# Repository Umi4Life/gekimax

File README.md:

# gekimax

generic rhythm game keypad controller with a lever

## BOM (LCSC, also see [the csv](gekimax-pcb/gekimax.csv))

| Part | Amount |
|---|---|
| RK09L11 Rotary Potentiometer | 1 |
| 100nF Capacitor 0805 | 28 |
| SK6812MINI-E LED | 21 |
| USB-C Connector | 5 |
| 220Ω Resistor 0603 | 1 |
| 5.1KΩ Resistor 0603 | 2 |

*RK09 potentiometer may need some disassembly and modding to remove detent*

## BOM (Additional Hardware)

| Part | Amount |
|---|---|
| Raspberry Pi Pico | 1 |
| M3 Heat Insert | 6 |
| M3 Nut | 2 |
| M3x15-16mm Countersunk Screw | 8 |
| M3x40 Button Head Screw | 1 |
| Rubber Feet | 4 |
| Rubber sheet/padding for lever | 1 |
| Keyboard Switches | 21 |
| Hot Swap Socket | 21 |
| Plate Mount Stabilizer | 4 |
| 1U keycaps | 8 |
| 1.25U keycaps | 9 |
| 2U keycaps | 2 |
| 2.75U keycaps | 2 |

## Notes
- Uses [GP2040-CE](https://gp2040-ce.info/) for firmware (need some manual key mapping)
- PCB has some additional side leds that I couldn't get them to work

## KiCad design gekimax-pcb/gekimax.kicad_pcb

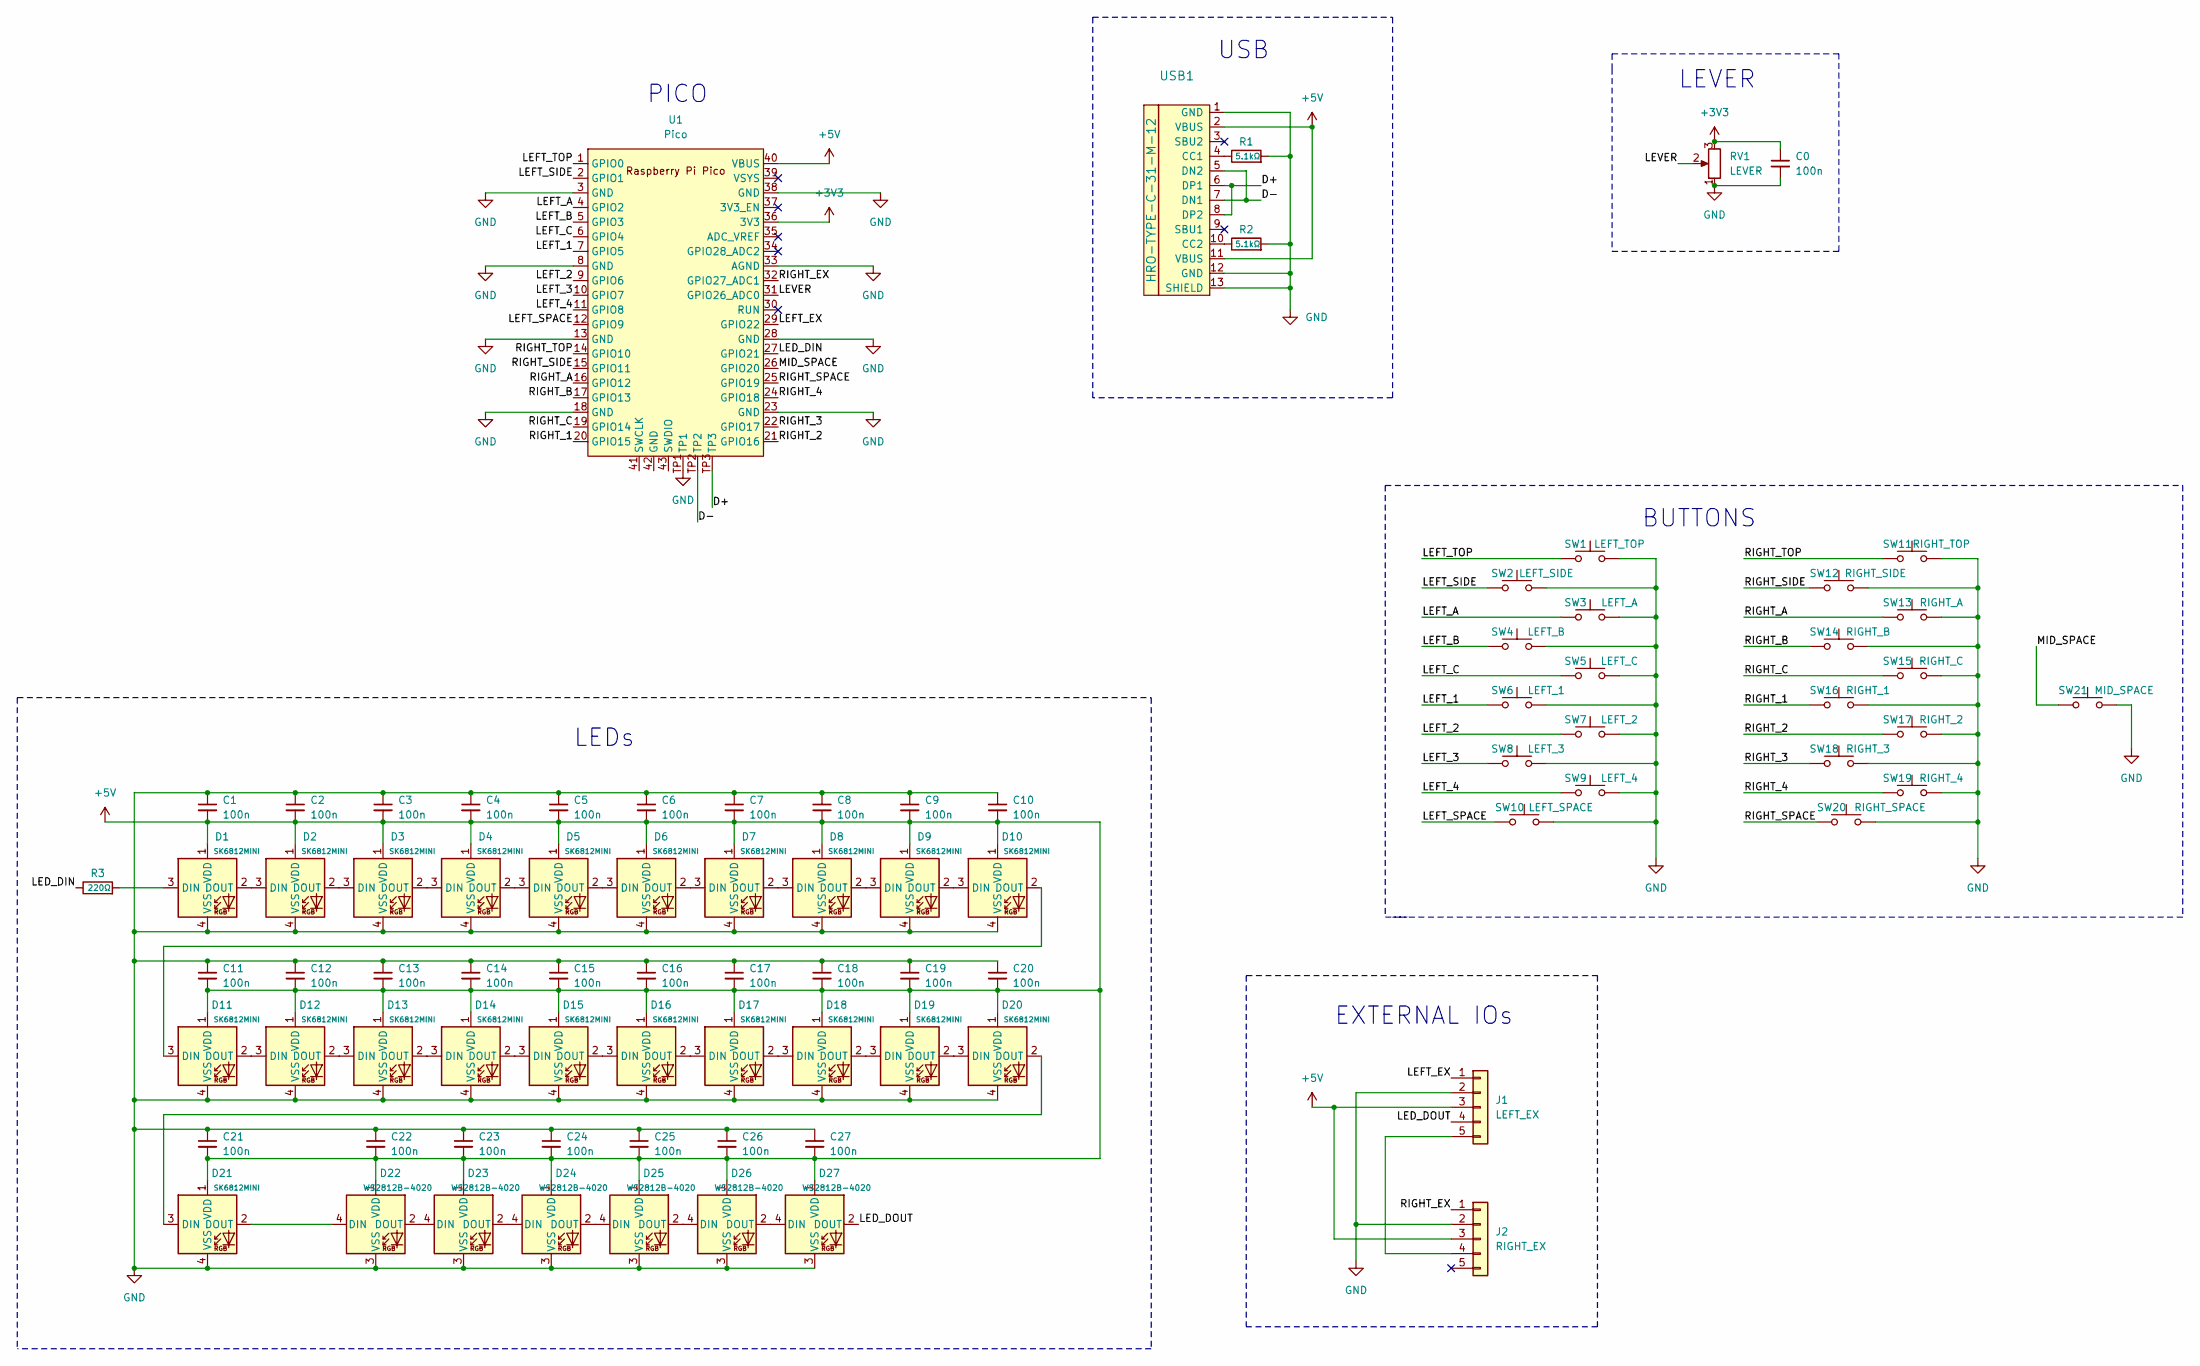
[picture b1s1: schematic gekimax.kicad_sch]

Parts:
C0, C1, C2, C3, C4, C5, C6, C7, C8, C9, C10, C11, C12, C13, C14, C15, C16, C17, C18, C19, C20, C21, C22, C23, C24, C25, C26, C27: 100n; C_0805_2012Metric_Pad1.18x1.45mm_HandSolder; LCSC C48579599
D1, D2, D3, D4, D5, D6, D7, D8, D9, D10, D11, D12, D13, D14, D15, D16, D17, D18, D19, D20, D21: SK6812MINI; LED_MX_6028R; LCSC C5149201
D22, D23, D24, D25, D26, D27: WS2812B-4020; LED_WS2812_4020; LCSC C965557
J1: LEFT_EX; JST_GH_SM05B-GHS-TB_1x05-1MP_P1.25mm_Horizontal; LCSC C189896
J2: RIGHT_EX; JST_GH_SM05B-GHS-TB_1x05-1MP_P1.25mm_Horizontal; LCSC C189896
R1, R2: 5.1kΩ; R_0603_1608Metric_Pad0.98x0.95mm_HandSolder; LCSC C2907044
R3: 220Ω; R_0603_1608Metric_Pad0.98x0.95mm_HandSolder; LCSC C107696
RV1: LEVER; Potentiometer_Alps_RK09L_Single_Horizontal; LCSC C2830189
SW1: LEFT_TOP; MX-Hotswap-1.25U
SW2: LEFT_SIDE; MX-Hotswap-2U
SW3: LEFT_A; MX-Hotswap-1.25U
SW4: LEFT_B; MX-Hotswap-1.25U
SW5: LEFT_C; MX-Hotswap-1.25U
SW6: LEFT_1; MX-Hotswap-1U
SW7: LEFT_2; MX-Hotswap-1U
SW8: LEFT_3; MX-Hotswap-1U
SW9: LEFT_4; MX-Hotswap-1U
SW10: LEFT_SPACE; MX-Hotswap-2U
SW11: RIGHT_TOP; MX-Hotswap-1.25U
SW12: RIGHT_SIDE; MX-Hotswap-2U
SW13: RIGHT_A; MX-Hotswap-1.25U
SW14: RIGHT_B; MX-Hotswap-1.25U
SW15: RIGHT_C; MX-Hotswap-1.25U
SW16: RIGHT_1; MX-Hotswap-1U
SW17: RIGHT_2; MX-Hotswap-1U
SW18: RIGHT_3; MX-Hotswap-1U
SW19: RIGHT_4; MX-Hotswap-1U
SW20: RIGHT_SPACE; MX-Hotswap-2U
SW21: MID_SPACE; MX-Hotswap-2U
U1: Pico; RPi_Pico_SMD
USB1: HRO-TYPE-C-31-M-12; HRO-TYPE-C-31-M-12-HandSoldering; LCSC C167321

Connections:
+3V3: C0.1, RV1.3, U1.36 (3V3)
+5V: C1.2, C2.2, C3.2, C4.2, C5.2, C6.2, C7.2, C8.2, C9.2, C10.2, C11.2, C12.2, C13.2, C14.2, C15.2, C16.2, C17.2, C18.2, C19.2, C20.2, C21.2, C22.2, C23.2, C24.2, C25.2, C26.2, C27.2, D1.1 (VDD), D2.1 (VDD), D3.1 (VDD), D4.1 (VDD), D5.1 (VDD), D6.1 (VDD), D7.1 (VDD), D8.1 (VDD), D9.1 (VDD), D10.1 (VDD), D11.1 (VDD), D12.1 (VDD), D13.1 (VDD), D14.1 (VDD), D15.1 (VDD), D16.1 (VDD), D17.1 (VDD), D18.1 (VDD), D19.1 (VDD), D20.1 (VDD), D21.1 (VDD), D22.1 (VDD), D23.1 (VDD), D24.1 (VDD), D25.1 (VDD), D26.1 (VDD), D27.1 (VDD), J1.3, J2.3, U1.40 (VBUS), USB1.2 (VBUS), USB1.11 (VBUS)
/D+: U1.TP3, USB1.6 (DP1), USB1.8 (DP2)
/D-: U1.TP2, USB1.5 (DN2), USB1.7 (DN1)
/LED_DIN: R3.1, U1.27 (GPIO21)
/LED_DOUT: D27.2 (DOUT), J1.4
/LEFT_1: SW6.1, U1.7 (GPIO5)
/LEFT_2: SW7.1, U1.9 (GPIO6)
/LEFT_3: SW8.1, U1.10 (GPIO7)
/LEFT_4: SW9.1, U1.11 (GPIO8)
/LEFT_A: SW3.1, U1.4 (GPIO2)
/LEFT_B: SW4.1, U1.5 (GPIO3)
/LEFT_C: SW5.1, U1.6 (GPIO4)
/LEFT_EX: J1.1, U1.29 (GPIO22)
/LEFT_SIDE: SW2.1, U1.2 (GPIO1)
/LEFT_SPACE: SW10.1, U1.12 (GPIO9)
/LEFT_TOP: SW1.1, U1.1 (GPIO0)
/LEVER: RV1.2, U1.31 (GPIO26_ADC0)
/MID_SPACE: SW21.1, U1.26 (GPIO20)
/RIGHT_1: SW16.1, U1.20 (GPIO15)
/RIGHT_2: SW17.1, U1.21 (GPIO16)
/RIGHT_3: SW18.1, U1.22 (GPIO17)
/RIGHT_4: SW19.1, U1.24 (GPIO18)
/RIGHT_A: SW13.1, U1.16 (GPIO12)
/RIGHT_B: SW14.1, U1.17 (GPIO13)
/RIGHT_C: SW15.1, U1.19 (GPIO14)
/RIGHT_EX: J2.1, U1.32 (GPIO27_ADC1)
/RIGHT_SIDE: SW12.1, U1.15 (GPIO11)
/RIGHT_SPACE: SW20.1, U1.25 (GPIO19)
/RIGHT_TOP: SW11.1, U1.14 (GPIO10)
GND: C0.2, C1.1, C2.1, C3.1, C4.1, C5.1, C6.1, C7.1, C8.1, C9.1, C10.1, C11.1, C12.1, C13.1, C14.1, C15.1, C16.1, C17.1, C18.1, C19.1, C20.1, C21.1, C22.1, C23.1, C24.1, C25.1, C26.1, C27.1, D1.4 (VSS), D2.4 (VSS), D3.4 (VSS), D4.4 (VSS), D5.4 (VSS), D6.4 (VSS), D7.4 (VSS), D8.4 (VSS), D9.4 (VSS), D10.4 (VSS), D11.4 (VSS), D12.4 (VSS), D13.4 (VSS), D14.4 (VSS), D15.4 (VSS), D16.4 (VSS), D17.4 (VSS), D18.4 (VSS), D19.4 (VSS), D20.4 (VSS), D21.4 (VSS), D22.3 (VSS), D23.3 (VSS), D24.3 (VSS), D25.3 (VSS), D26.3 (VSS), D27.3 (VSS), J1.2, J2.2, R1.2, R2.2, RV1.1, SW1.2, SW2.2, SW3.2, SW4.2, SW5.2, SW6.2, SW7.2, SW8.2, SW9.2, SW10.2, SW11.2, SW12.2, SW13.2, SW14.2, SW15.2, SW16.2, SW17.2, SW18.2, SW19.2, SW20.2, SW21.2, U1.3 (GND), U1.8 (GND), U1.13 (GND), U1.18 (GND), U1.23 (GND), U1.28 (GND), U1.33 (AGND), U1.38 (GND), U1.TP1, USB1.1 (GND), USB1.12 (GND), USB1.13 (SHIELD)
unnamed: D1.3 (DIN), R3.2
unnamed: D1.2 (DOUT), D2.3 (DIN)
unnamed: D2.2 (DOUT), D3.3 (DIN)
unnamed: D3.2 (DOUT), D4.3 (DIN)
unnamed: D4.2 (DOUT), D5.3 (DIN)
unnamed: D5.2 (DOUT), D6.3 (DIN)
unnamed: D6.2 (DOUT), D7.3 (DIN)
unnamed: D7.2 (DOUT), D8.3 (DIN)
unnamed: D8.2 (DOUT), D9.3 (DIN)
unnamed: D9.2 (DOUT), D10.3 (DIN)
unnamed: D10.2 (DOUT), D11.3 (DIN)
unnamed: D11.2 (DOUT), D12.3 (DIN)
unnamed: D12.2 (DOUT), D13.3 (DIN)
unnamed: D13.2 (DOUT), D14.3 (DIN)
unnamed: D14.2 (DOUT), D15.3 (DIN)
unnamed: D15.2 (DOUT), D16.3 (DIN)
unnamed: D16.2 (DOUT), D17.3 (DIN)
unnamed: D17.2 (DOUT), D18.3 (DIN)
unnamed: D18.2 (DOUT), D19.3 (DIN)
unnamed: D19.2 (DOUT), D20.3 (DIN)
unnamed: D20.2 (DOUT), D21.3 (DIN)
unnamed: D21.2 (DOUT), D22.4 (DIN)
unnamed: D22.2 (DOUT), D23.4 (DIN)
unnamed: D23.2 (DOUT), D24.4 (DIN)
unnamed: D24.2 (DOUT), D25.4 (DIN)
unnamed: D25.2 (DOUT), D26.4 (DIN)
unnamed: D26.2 (DOUT), D27.4 (DIN)
unnamed: J1.5, J2.4
unnamed: R1.1, USB1.4 (CC1)
unnamed: R2.1, USB1.10 (CC2)

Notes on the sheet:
USB
PICO
BUTTONS
LEDs
EXTERNAL IOs
LEVER

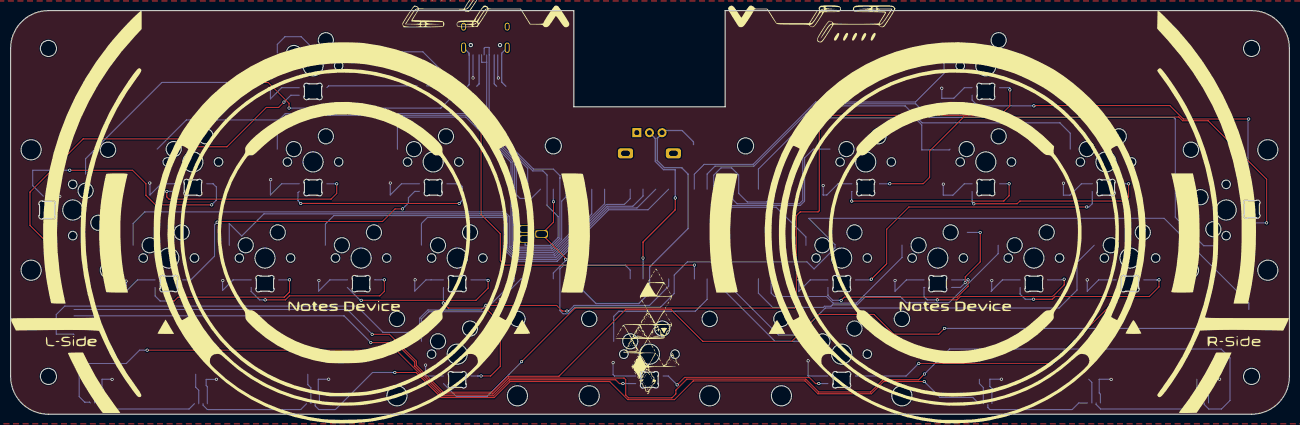
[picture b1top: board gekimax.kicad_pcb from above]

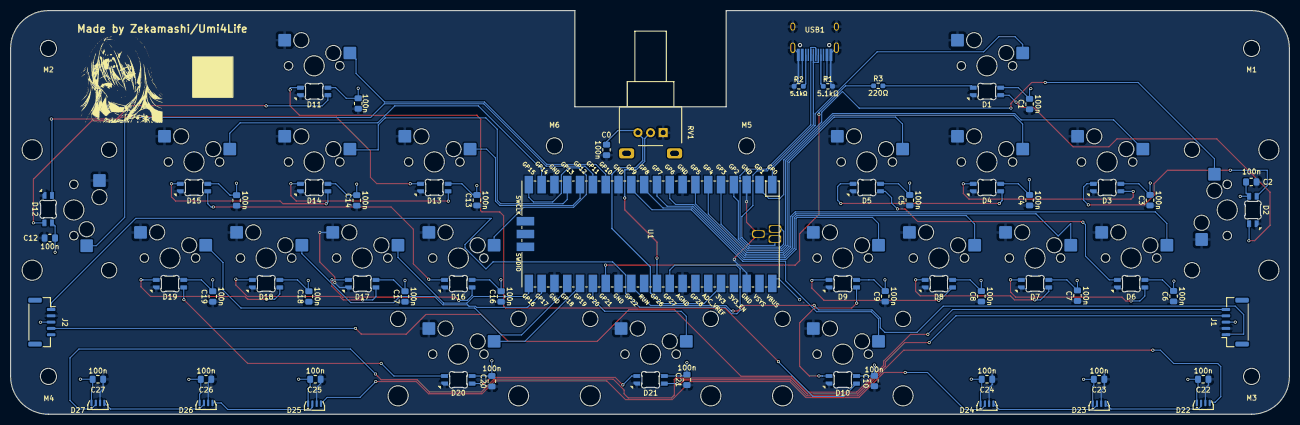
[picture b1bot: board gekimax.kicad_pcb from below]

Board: 2 copper layers, 253.5 x 80.0 mm, 90 parts (69 on the bottom side), 61 nets.

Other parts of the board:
M1, M2, M3, M4, M5, M6: MountingHole_3.2mm_M3
